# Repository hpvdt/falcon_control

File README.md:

>[!WARNING]
>The functionality of this board has been split between the new wing modules and flight sticks, so this hardware is redundant and will no longer be worked on.

# Control Board

This board is primarily meant to collect the inputs from the flight sticks over I2C and then operate control surface servos. In addition to this it also has the functionlity to read potentiometers on the control surfaces to verify the control surfaces are moving into the right position and even alerting the pilots if they fail to using a buzzer for attention and LEDs to specify the problematic surfaces.

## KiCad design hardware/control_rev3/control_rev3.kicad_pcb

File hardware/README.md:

# Hardware

KiCad projects for the control boards.

## Revision 3

Most recent board. Current candidate for installation into Falcon.

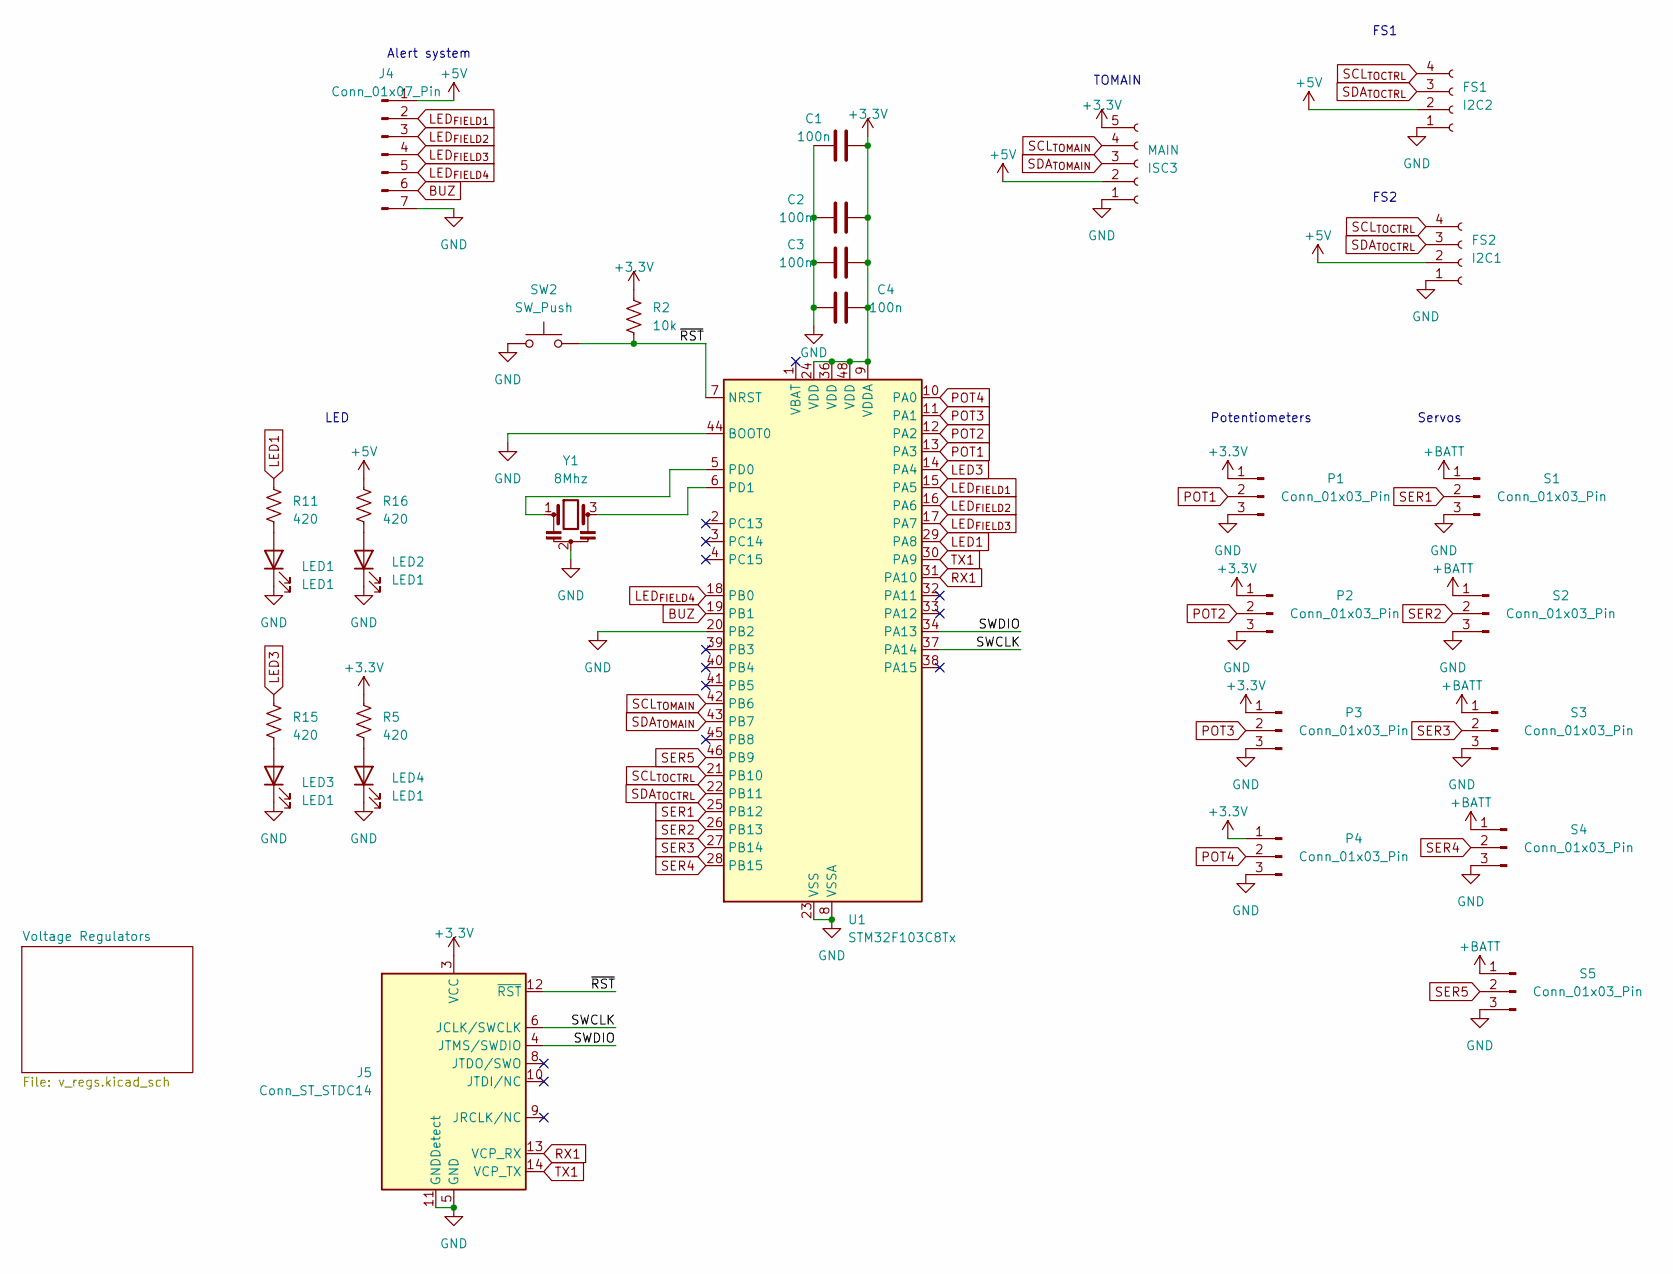
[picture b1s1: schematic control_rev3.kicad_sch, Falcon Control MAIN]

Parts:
C1, C2, C3, C4: 100n; C_0603_1608Metric
I2C1: FS2; JST_XH_B4B-XH-A_1x04_P2.50mm_Vertical
I2C2: FS1; JST_XH_B4B-XH-A_1x04_P2.50mm_Vertical
ISC3: MAIN; JST_XH_B5B-XH-A_1x05_P2.50mm_Vertical
J4: Conn_01x07_Pin; JST_XH_B7B-XH-A_1x07_P2.50mm_Vertical
J5: Conn_ST_STDC14; PinHeader_2x07_P1.27mm_Vertical_SMD
LED1, LED2, LED3, LED4: LED1; LED_0805_2012Metric_Pad1.15x1.40mm_HandSolder
P1, P2, P3, P4: Conn_01x03_Pin; JST_EH_B3B-EH-A_1x03_P2.50mm_Vertical
R2: 10k; R_0603_1608Metric
R5, R11, R15, R16: 420; R_0603_1608Metric
S1, S2, S3, S4, S5: Conn_01x03_Pin; JST_EH_B3B-EH-A_1x03_P2.50mm_Vertical
SW2: SW_Push; SW_SPST_B3U-1000P-B
U1: STM32F103C8Tx; LQFP-48_7x7mm_P0.5mm
Y1: 8Mhz; Resonator_SMD_Murata_CSTxExxV-3Pin_3.0x1.1mm

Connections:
+3.3V: C1.2, C2.2, C3.2, C4.1, ISC3.5, J5.3 (VCC), P1.1, P2.1, P3.1, P4.1, R2.1, R5.2, U1.9 (VDDA), U1.24 (VDD), U1.36 (VDD), U1.48 (VDD); also elsewhere on the board
+5V: I2C1.2, I2C2.2, ISC3.2, J4.1, R16.2; also elsewhere on the board
+BATT: S1.1, S2.1, S3.1, S4.1, S5.1; also elsewhere on the board
/SWCLK: J5.6 (JCLK/SWCLK), U1.37 (PA14)
/SWDIO: J5.4 (JTMS/SWDIO), U1.34 (PA13)
/~RST: J5.12 (~RST), R2.2, SW2.2, U1.7 (NRST)
BUZ: J4.6, U1.19 (PB1)
GND: C1.1, C2.1, C3.1, C4.2, I2C1.1, I2C2.1, ISC3.1, J4.7, J5.5 (GND), J5.7 (GND), J5.11 (GNDDetect), LED1.1 (K), LED2.1 (K), LED3.1 (K), LED4.1 (K), P1.3, P2.3, P3.3, P4.3, S1.3, S2.3, S3.3, S4.3, S5.3, SW2.1, U1.8 (VSSA), U1.20 (PB2), U1.23 (VSS), U1.35 (VSS), U1.44 (BOOT0), U1.47 (VSS), Y1.2; also elsewhere on the board
LED1: R11.2, U1.29 (PA8)
LED3: R15.2, U1.14 (PA4)
LED_{FIELD1}: J4.2, U1.15 (PA5)
LED_{FIELD2}: J4.3, U1.16 (PA6)
LED_{FIELD3}: J4.4, U1.17 (PA7)
LED_{FIELD4}: J4.5, U1.18 (PB0)
unnamed: LED1.2 (A), R11.1
unnamed: LED2.2 (A), R16.1
unnamed: LED3.2 (A), R15.1
unnamed: LED4.2 (A), R5.1
unnamed: U1.5 (PD0), Y1.1
unnamed: U1.6 (PD1), Y1.3
POT1: P1.2, U1.13 (PA3)
POT2: P2.2, U1.12 (PA2)
POT3: P3.2, U1.11 (PA1)
POT4: P4.2, U1.10 (PA0)
RX1: J5.13 (VCP_RX), U1.31 (PA10)
SCL_{TOCTRL}: I2C1.4, I2C2.4, U1.21 (PB10)
SCL_{TOMAIN}: ISC3.4, U1.42 (PB6)
SDA_{TOCTRL}: I2C1.3, I2C2.3, U1.22 (PB11)
SDA_{TOMAIN}: ISC3.3, U1.43 (PB7)
SER1: S1.2, U1.25 (PB12)
SER2: S2.2, U1.26 (PB13)
SER3: S3.2, U1.27 (PB14)
SER4: S4.2, U1.28 (PB15)
SER5: S5.2, U1.46 (PB9)
TX1: J5.14 (VCP_TX), U1.30 (PA9)

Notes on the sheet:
FS1
Servos
Alert system
FS2
TOMAIN
Potentiometers
LED

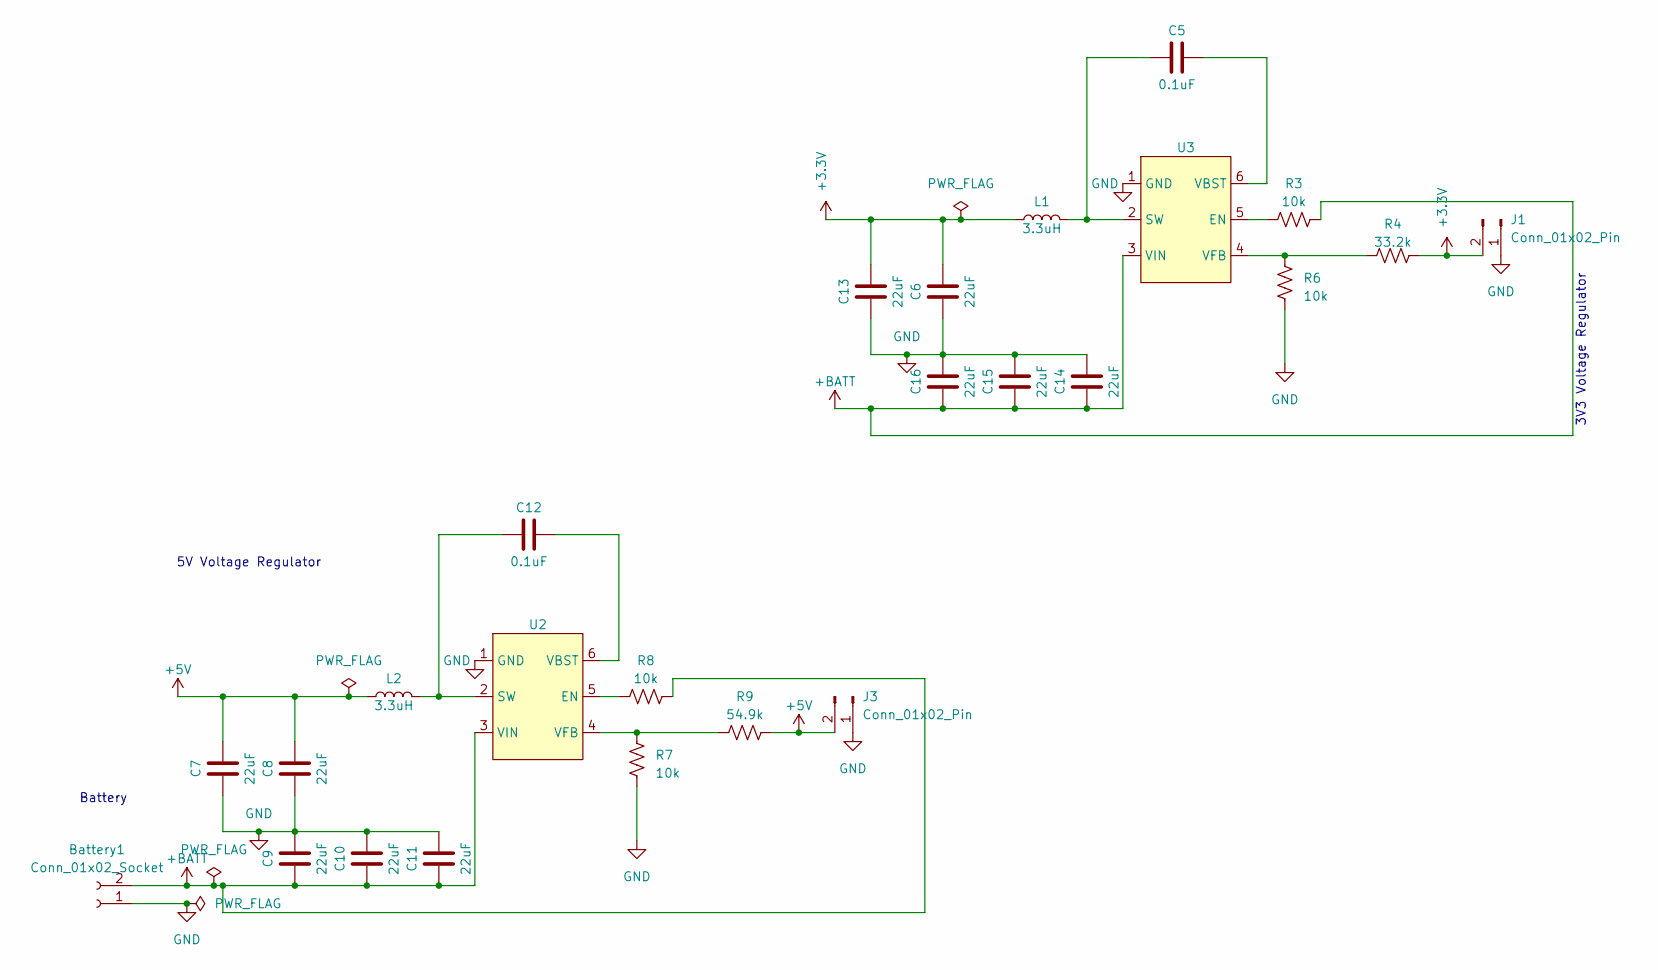
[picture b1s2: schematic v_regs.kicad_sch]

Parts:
Battery1: Conn_01x02_Socket; AMASS_XT60-M_1x02_P7.20mm_Vertical
C5, C12: 0.1uF; C_0805_2012Metric
C6, C7, C8, C9, C10, C11, C13, C14, C15, C16: 22uF; C_0805_2012Metric
J1, J3: Conn_01x02_Pin; JST_XH_B2B-XH-A_1x02_P2.50mm_Vertical
L1, L2: 3.3uH; L_Taiyo-Yuden_NR-60xx
R3, R6, R7, R8: 10k; R_0603_1608Metric
R4: 33.2k; R_0603_1608Metric
R9: 54.9k; R_0603_1608Metric
U2, U3: TSOT-23-6

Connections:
+3.3V: C6.2, C13.2, J1.2, L1.1, R4.1; also elsewhere on the board
+5V: C7.2, C8.2, J3.2, L2.1, R9.1; also elsewhere on the board
+BATT: Battery1.2, C9.1, C10.1, C11.1, C14.1, C15.1, C16.1, R3.2, R8.2, U2.3 (VIN), U3.3 (VIN); also elsewhere on the board
GND: Battery1.1, C6.1, C7.1, C8.1, C9.2, C10.2, C11.2, C13.1, C14.2, C15.2, C16.2, J1.1, J3.1, R6.1, R7.1, U2.1 (GND), U3.1 (GND); also elsewhere on the board
unnamed: R8.1, U2.5 (EN)
unnamed: C12.1, L2.2, U2.2 (SW)
unnamed: C12.2, U2.6 (VBST)
unnamed: R7.2, R9.2, U2.4 (VFB)
unnamed: R3.1, U3.5 (EN)
unnamed: C5.1, L1.2, U3.2 (SW)
unnamed: C5.2, U3.6 (VBST)
unnamed: R4.2, R6.2, U3.4 (VFB)

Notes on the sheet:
5V Voltage Regulator
3V3 Voltage Regulator
Battery

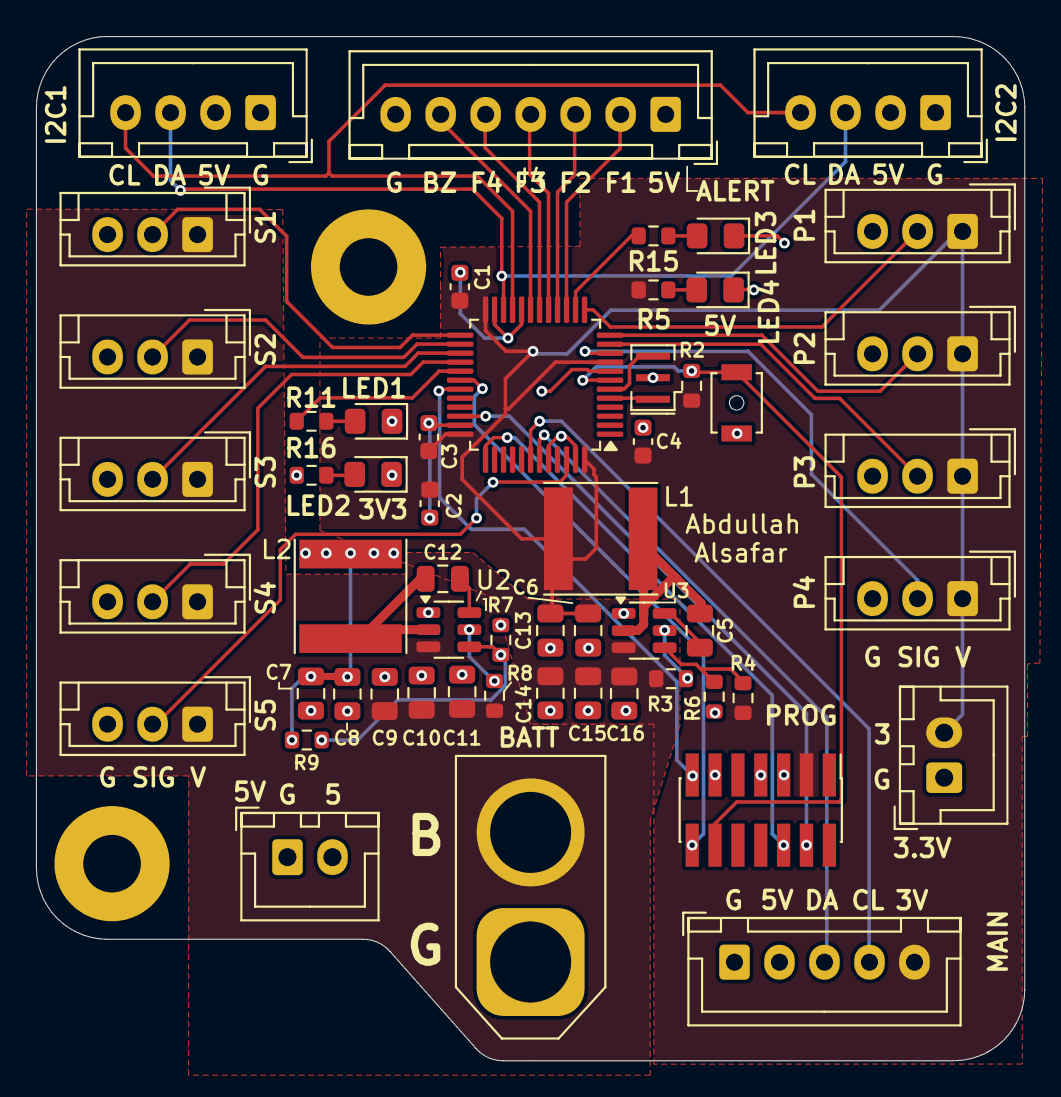
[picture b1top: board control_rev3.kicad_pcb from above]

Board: 2 copper layers, 54.9 x 56.9 mm, 55 parts (0 on the bottom side), 43 nets.

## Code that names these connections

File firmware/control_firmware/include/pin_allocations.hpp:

#ifndef CONTROL_PIN_ALLOCATIONS_H
#define CONTROL_PIN_ALLOCATIONS_H

#include <Arduino.h>

#define PIN_DEBUG_RX PA10
#define PIN_DEBUG_TX PA9

#define PIN_MAIN_SDA PB7
#define PIN_MAIN_SCL PB6

#define PIN_CONTROLLER_SDA PB11
#define PIN_CONTROLLER_SCL PB10

#define PIN_BUZZER PB1

#define PIN_LED_STATUS_1 PA8
#define PIN_LED_STATUS_2 PA4

#define NUM_SERVOS 5
#define PIN_SERVO_1 PB12
#define PIN_SERVO_2 PB13
#define PIN_SERVO_3 PB14
#define PIN_SERVO_4 PB15
#define PIN_SERVO_5 PB9

#define NUM_POTENTIOMETERS 4
#define PIN_POTENTIOMETER_1 PA3
#define PIN_POTENTIOMETER_2 PA2
#define PIN_POTENTIOMETER_3 PA1
#define PIN_POTENTIOMETER_4 PA0

#define NUM_LED_FIELDS 4
#define PIN_LED_FIELD_1 PA5
#define PIN_LED_FIELD_2 PA6
#define PIN_LED_FIELD_3 PA7
#define PIN_LED_FIELD_4 PB0
#define PIN_LED_FIELD_ACTIVE HIGH

extern const int PIN_SERVOS[NUM_SERVOS];
extern const int PIN_POTENTIOMETERS[NUM_POTENTIOMETERS];
extern const int PIN_LED_FIELD[NUM_LED_FIELDS];

#endif

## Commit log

2023-09-24 Initializatrion of PlatformIO project
2023-11-08 Update platformio.ini
    Made debugging more generic
2024-01-24 Touch ups from testing
2024-03-02 Updated code
2024-03-16 added potentiometers & added conditionals for LEDs
2025-08-05 Arranged files in new scheme
2025-08-05 Updated to KiCad 9
2025-08-05 Centralized pin allocations
2025-08-07 Migrated some surface check functions
2025-08-08 Tidied up control surface setting calls
2025-08-09 Changed boot to flash/buzz
2025-08-09 Drafted I2C comms to flight sticks
2025-08-09 Changed to 4 space indenting
2025-08-09 Reorganized the main code
2025-08-09 Created dedicated header for flight stick state for easier reuse
2025-08-17 Added servo sweep test
